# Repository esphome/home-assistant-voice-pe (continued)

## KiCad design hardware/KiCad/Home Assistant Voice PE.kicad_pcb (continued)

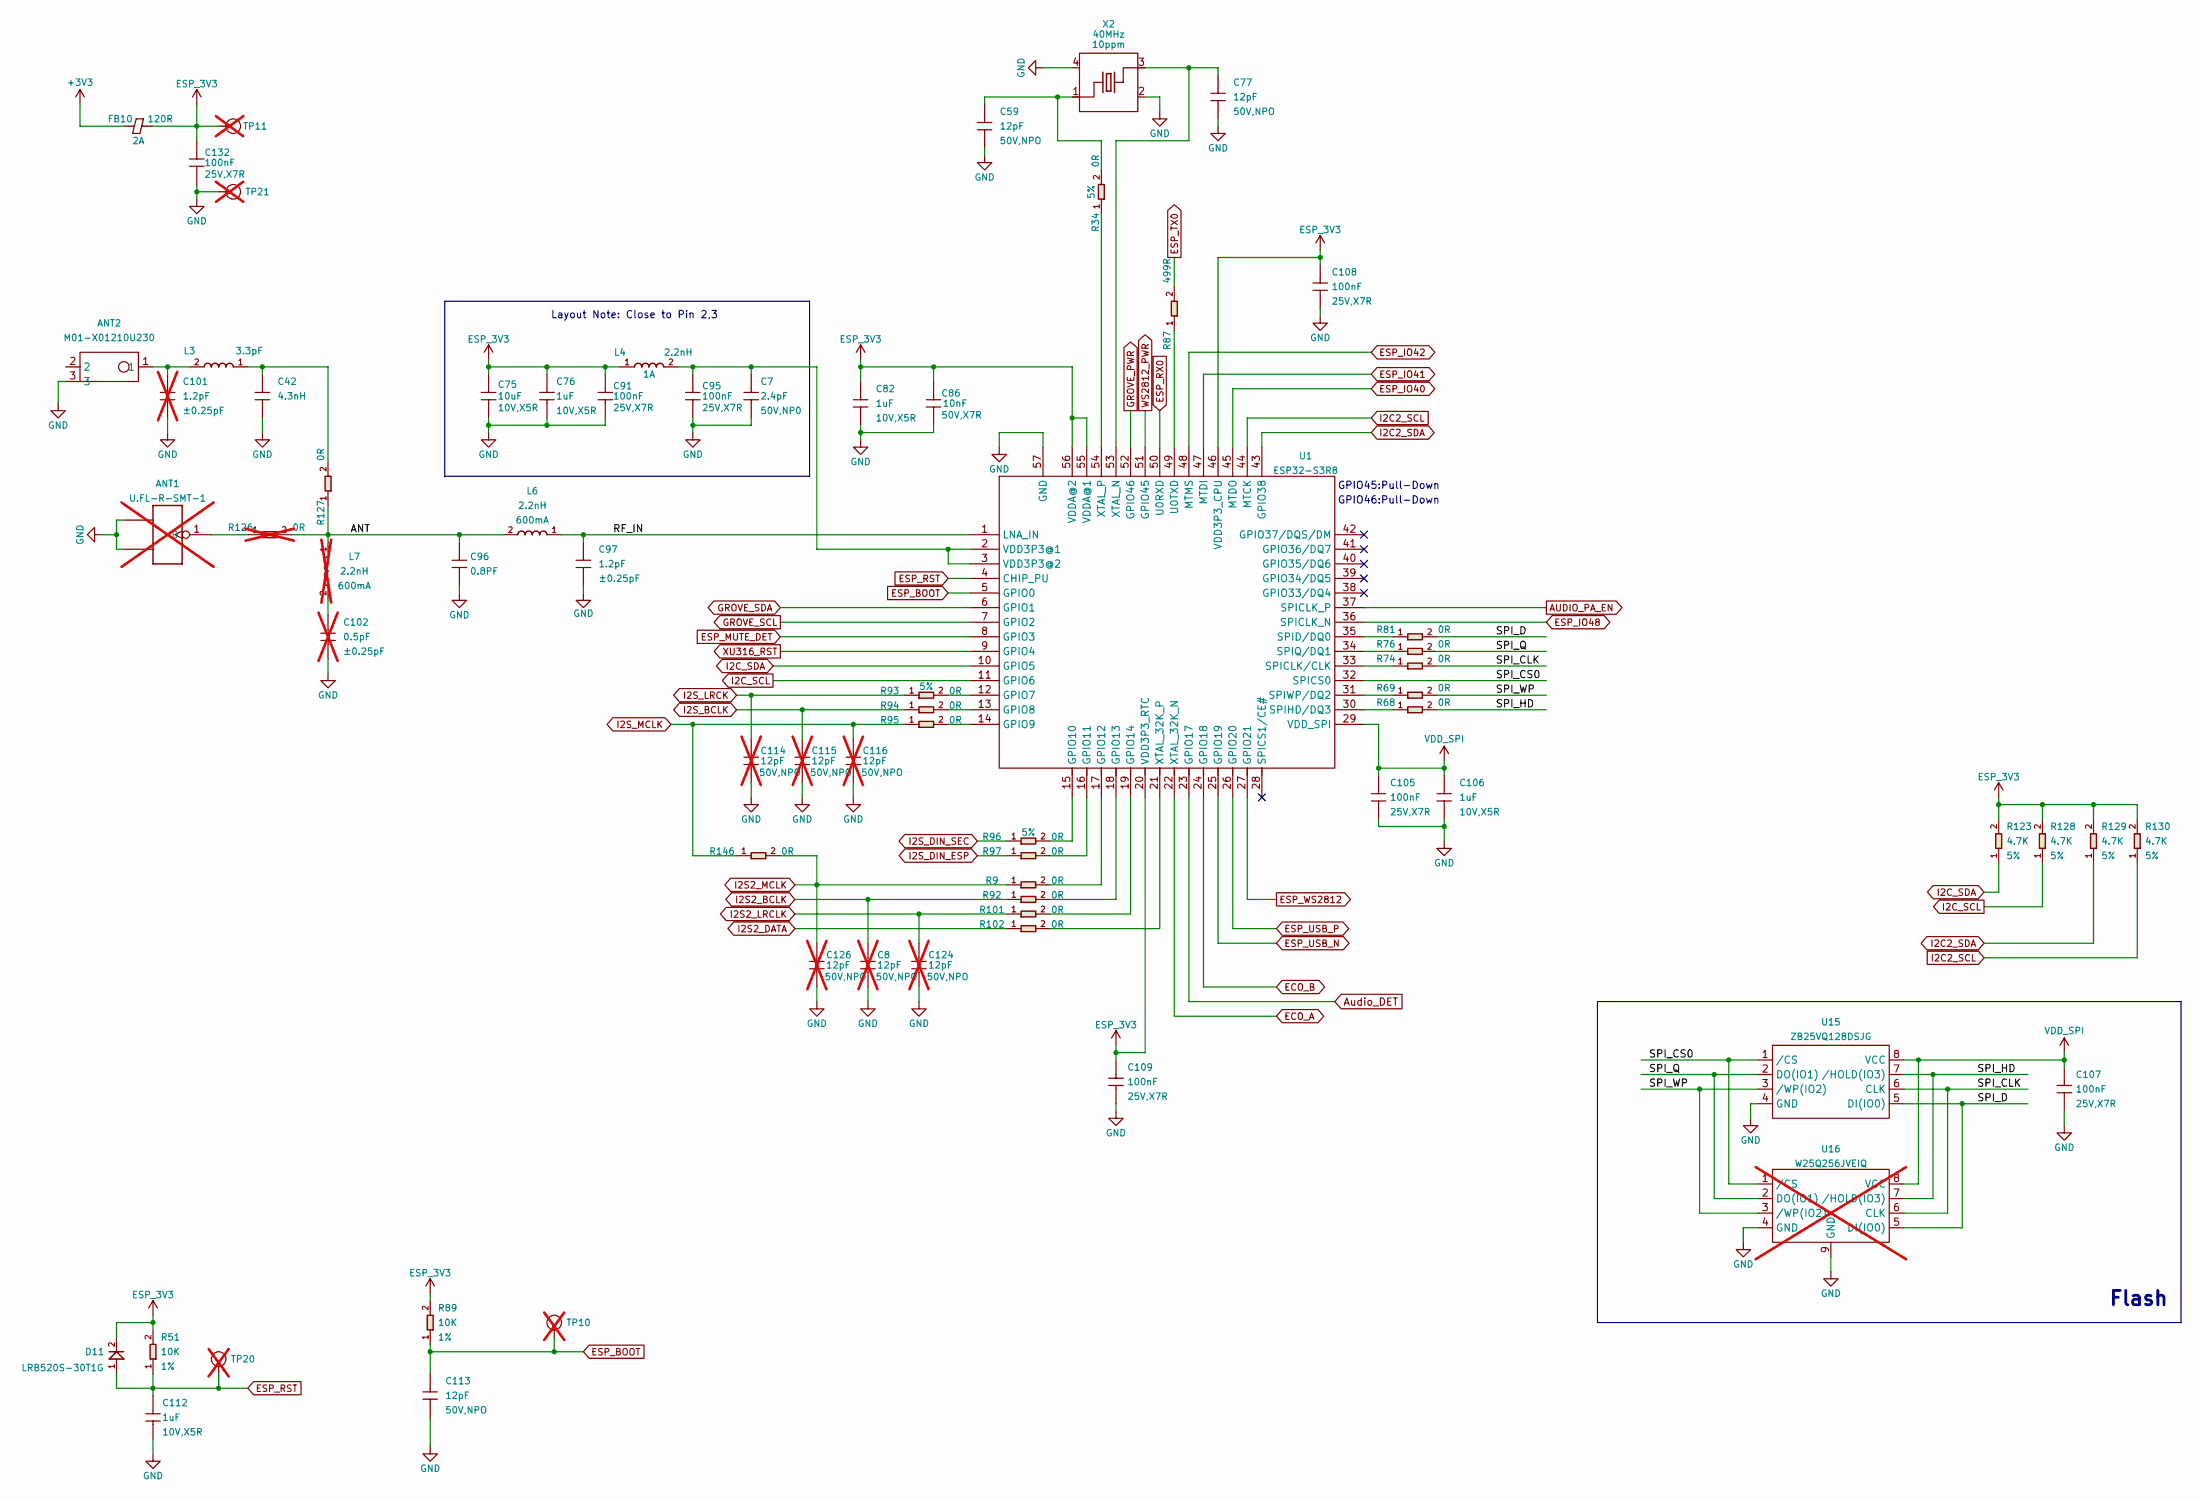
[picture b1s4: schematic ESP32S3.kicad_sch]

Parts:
ANT1: U.FL-R-SMT-1; U-FL3P-SMD-2.6X2.6X1.0MM; MPN U.FL-R-SMT-1; not fitted
ANT2: M01-X01210U230; ANT2P-12x10.45x3.0MM_3; MPN M01-X01210U230
C7: 2.4pF; C0402; Voltage Rating 50V,NP0; MPN CC0402CRNPO9BN2R4
C8, C114, C115, C116, C124, C126: 12pF; C0402; Voltage Rating 50V,NPO; MPN CC0402JRNPO9BN120; not fitted
C42: 4.3nH; C0201; MPN LQP03TN4N3H02D
C59, C77, C113: 12pF; C0402; Voltage Rating 50V,NPO; MPN CC0402JRNPO9BN120
C75: 10uF; C0603; Voltage Rating 10V,X5R; MPN CL10A106KP8NNNC
C76, C82, C106, C112: 1uF; C0402; Voltage Rating 10V,X5R; MPN CL05A105KP5NNNC
C86: 10nF; C0402; Voltage Rating 50V,X7R; MPN CC0402KRX7R9BB103
C91, C95, C105, C107, C108, C109, C132: 100nF; C0402; Voltage Rating 25V,X7R; MPN CC0402KRX7R8BB104
C96: 0.8PF; C0201; Voltage Rating 50V-0.01pF-C0G/NP0; MPN GRM0335C1HR80BA01D
C97: 1.2pF; C0201; Voltage Rating ±0.25pF; MPN CC0201CRNPO9BN1R2
C101: 1.2pF; C0201; Voltage Rating ±0.25pF; MPN CC0201CRNPO9BN1R2; not fitted
C102: 0.5pF; C0201; Voltage Rating ±0.25pF; MPN CC0201CRNPO9BN1R2; not fitted
D11: LRB520S-30T1G; SOD-523; Rating 30V,200mA; MPN LRB520S-30T1G
FB10: 120R; L0603; Rating 2A; MPN BLM18PG121SN1D
L3: 3.3pF; L0201; MPN CQ0201BRNPO8BN3R3
L4: 2.2nH; L0402; Rating 1A; MPN LQW15AN2N2C10D
L6: 2.2nH; L0201; Rating 600mA; MPN LQP03TQ2N2B02D
L7: 2.2nH; L0201; Rating 600mA; MPN LQP03TN1N5B02D; not fitted
R9, R34, R92, R93, R94, R95, R96, R97, R101, R102, R146: 0R; R0402; Power Rating 5%; MPN RC0402JR-070RL
R51, R89: 10K; R0402; Power Rating 1%; MPN RC0402FR-0710KL
R68, R69, R74, R76, R81, R127: 0R; R0201; Power Rating 1%; MPN RC0201FR-070RL
R87: 499R; R0402; Power Rating 1%; MPN RC0402FR-07499RL
R123, R128, R129, R130: 4.7K; R0402; Power Rating 5%; MPN RC0402JR-074K7L
R126: 0R; R0201; Power Rating 1%; MPN RC0201FR-070RL; not fitted
TP10, TP20, TP21: Test Point; TP-D45MIL; Part Type Test Point; not fitted
TP11: TEST-POINT; TP-D45MIL; not fitted
U1: ESP32-S3R8; QFN56G-0.4-7X7MM; MPN ESP32-S3R8
U15: ZB25VQ128DSJG; SOIC8-1.27-5.3X5.3MM; MPN ZB25VQ128DSJG
U16: W25Q256JVEIQ; WSON8-1.27-8x6x0.75mm; MPN W25Q256JVEIQ; not fitted
X2: 40MHz; X4-SMD-2.0X1.6MM; Rating 10ppm; MPN Y4000Fc001

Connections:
+3V3: FB10.1; also elsewhere on the board
/ESP32/ANT: C96.1, L6.2, L7.1, R126.2, R127.1
/ESP32/RF_IN: C97.1, L6.1, U1.1 (LNA_IN)
/ESP32/SPI_CLK: R74.2, U15.6 (CLK), U16.6 (CLK)
/ESP32/SPI_CS0: U1.32 (SPICS0), U15.1 (/CS), U16.1 (/CS)
/ESP32/SPI_D: R81.2, U15.5 (DI(IO0)), U16.5 (DI(IO0))
/ESP32/SPI_HD: R68.2, U15.7 (/HOLD(IO3)), U16.7 (/HOLD(IO3))
/ESP32/SPI_Q: R76.2, U15.2 (DO(IO1)), U16.2 (DO(IO1))
/ESP32/SPI_WP: R69.2, U15.3 (/WP(IO2)), U16.3 (/WP(IO2))
AUDIO_PA_EN: U1.37 (SPICLK_P); also elsewhere on the board
Audio_DET: U1.23 (GPIO17); also elsewhere on the board
ECO_A: U1.22 (XTAL_32K_N); also elsewhere on the board
ECO_B: U1.24 (GPIO18); also elsewhere on the board
ESP_3V3: C75.1, C76.1, C82.1, C86.1, C91.1, C108.1, C109.1, C132.1, D11.2, FB10.2, L4.1, R51.2, R89.2, R123.2, R128.2, R129.2, R130.2, TP11.1 (T), U1.20 (VDD3P3_RTC), U1.46 (VDD3P3_CPU), U1.55 (VDDA@1), U1.56 (VDDA@2); also elsewhere on the board
ESP_BOOT: C113.1, R89.1, TP10.1 (T), U1.5 (GPIO0); also elsewhere on the board
ESP_IO40: U1.45 (MTDO); also elsewhere on the board
ESP_IO41: U1.47 (MTDI); also elsewhere on the board
ESP_IO42: U1.48 (MTMS); also elsewhere on the board
ESP_IO48: U1.36 (SPICLK_N); also elsewhere on the board
ESP_MUTE_DET: U1.8 (GPIO3); also elsewhere on the board
ESP_RST: C112.1, D11.1, R51.1, TP20.1 (T), U1.4 (CHIP_PU)
ESP_RX0: U1.50 (U0RXD); also elsewhere on the board
ESP_TX0: R87.2; also elsewhere on the board
ESP_USB_N: U1.25 (GPIO19); also elsewhere on the board
ESP_USB_P: U1.26 (GPIO20); also elsewhere on the board
ESP_WS2812: U1.27 (GPIO21); also elsewhere on the board
GND: ANT1.2 (GND1), ANT1.3 (GND2), ANT2.3, C7.2, C8.2, C42.2, C59.2, C75.2, C76.2, C77.2, C82.2, C86.2, C91.2, C95.2, C96.2, C97.2, C101.2, C102.2, C105.2, C106.2, C107.2, C108.2, C109.2, C112.2, C113.2, C114.2, C115.2, C116.2, C124.2, C126.2, C132.2, TP21.1 (T), U1.57 (GND), U15.4 (GND), U16.4 (GND), U16.9 (GND), X2.2, X2.4; also elsewhere on the board
GROVE_PWR: U1.52 (GPIO46); also elsewhere on the board
GROVE_SCL: U1.7 (GPIO2); also elsewhere on the board
GROVE_SDA: U1.6 (GPIO1); also elsewhere on the board
I2C2_SCL: R130.1, U1.44 (MTCK); also elsewhere on the board
I2C2_SDA: R129.1, U1.43 (GPIO38); also elsewhere on the board
I2C_SCL: R128.1, U1.11 (GPIO6); also elsewhere on the board
I2C_SDA: R123.1, U1.10 (GPIO5); also elsewhere on the board
I2S2_BCLK: C8.1, R92.1; also elsewhere on the board
I2S2_DATA: R102.1; also elsewhere on the board
I2S2_LRCLK: C124.1, R101.1; also elsewhere on the board
I2S2_MCLK: C126.1, R9.1, R146.2; also elsewhere on the board
I2S_BCLK: C115.1, R94.1; also elsewhere on the board
I2S_DIN_ESP: R97.1; also elsewhere on the board
I2S_DIN_SEC: R96.1; also elsewhere on the board
I2S_LRCK: C114.1, R93.1; also elsewhere on the board
I2S_MCLK: C116.1, R95.1, R146.1; also elsewhere on the board
unnamed: ANT1.1 (D), R126.1
unnamed: ANT2.1, C101.1, L3.2
unnamed: C42.1, L3.1, R127.2
unnamed: C59.1, R34.2, X2.1
unnamed: C102.1, L7.2
unnamed: R93.2, U1.12 (GPIO7)
unnamed: R94.2, U1.13 (GPIO8)
unnamed: R95.2, U1.14 (GPIO9)
unnamed: R96.2, U1.15 (GPIO10)
unnamed: R97.2, U1.16 (GPIO11)
unnamed: R9.2, U1.17 (GPIO12)
unnamed: R92.2, U1.18 (GPIO13)
unnamed: R101.2, U1.19 (GPIO14)
unnamed: R74.1, U1.33 (SPICLK/CLK)
unnamed: R81.1, U1.35 (SPID/DQ0)
unnamed: R68.1, U1.30 (SPIHD/DQ3)
unnamed: R76.1, U1.34 (SPIQ/DQ1)
unnamed: R69.1, U1.31 (SPIWP/DQ2)
unnamed: R87.1, U1.49 (U0TXD)
unnamed: C7.1, C95.1, L4.2, U1.2 (VDD3P3@1), U1.3 (VDD3P3@2)
unnamed: R102.2, U1.21 (XTAL_32K_P)
unnamed: C77.1, U1.53 (XTAL_N), X2.3
unnamed: R34.1, U1.54 (XTAL_P)
VDD_SPI: C105.1, C106.1, C107.1, U1.29 (VDD_SPI), U15.8 (VCC), U16.8 (VCC)
WS2812_PWR: U1.51 (GPIO45); also elsewhere on the board
XU316_RST: U1.9 (GPIO4); also elsewhere on the board

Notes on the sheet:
GPIO45:Pull-Down
Layout Note: Close to Pin 2,3
GPIO46:Pull-Down
Flash

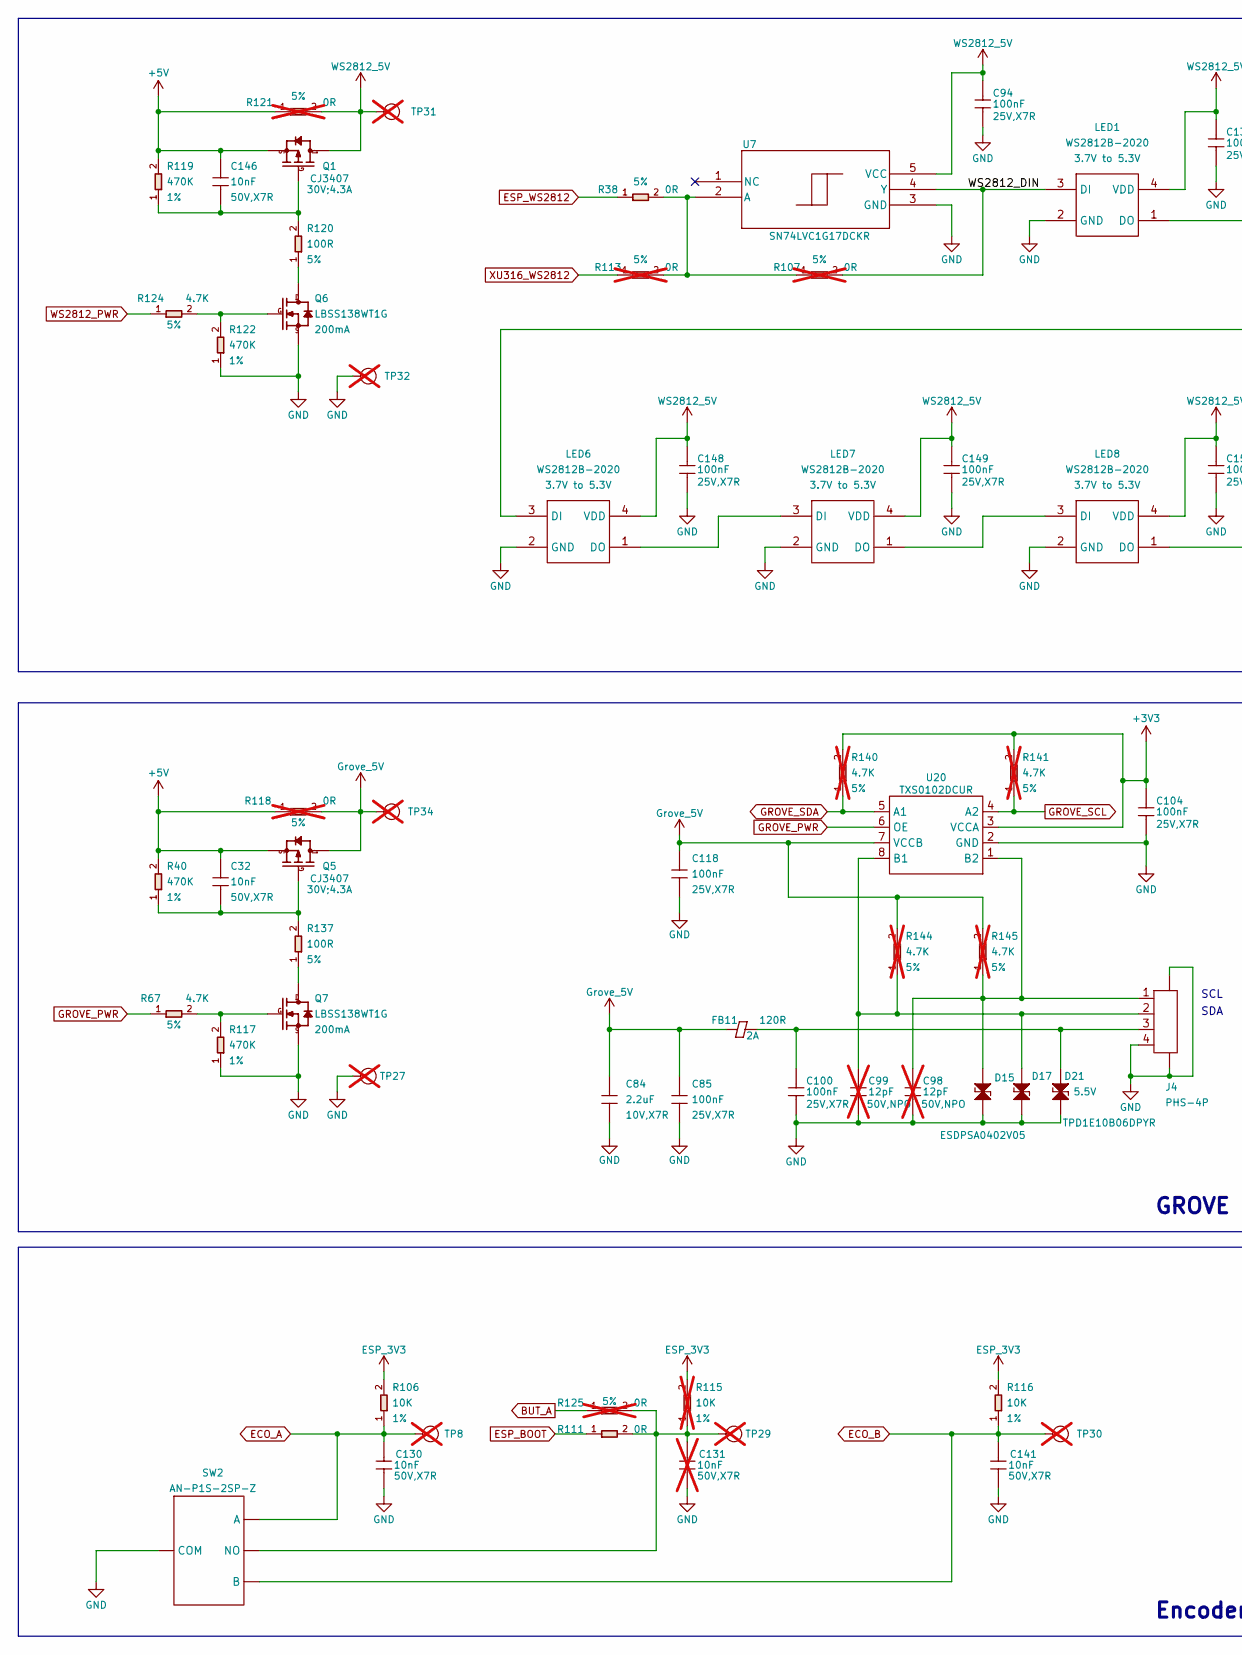
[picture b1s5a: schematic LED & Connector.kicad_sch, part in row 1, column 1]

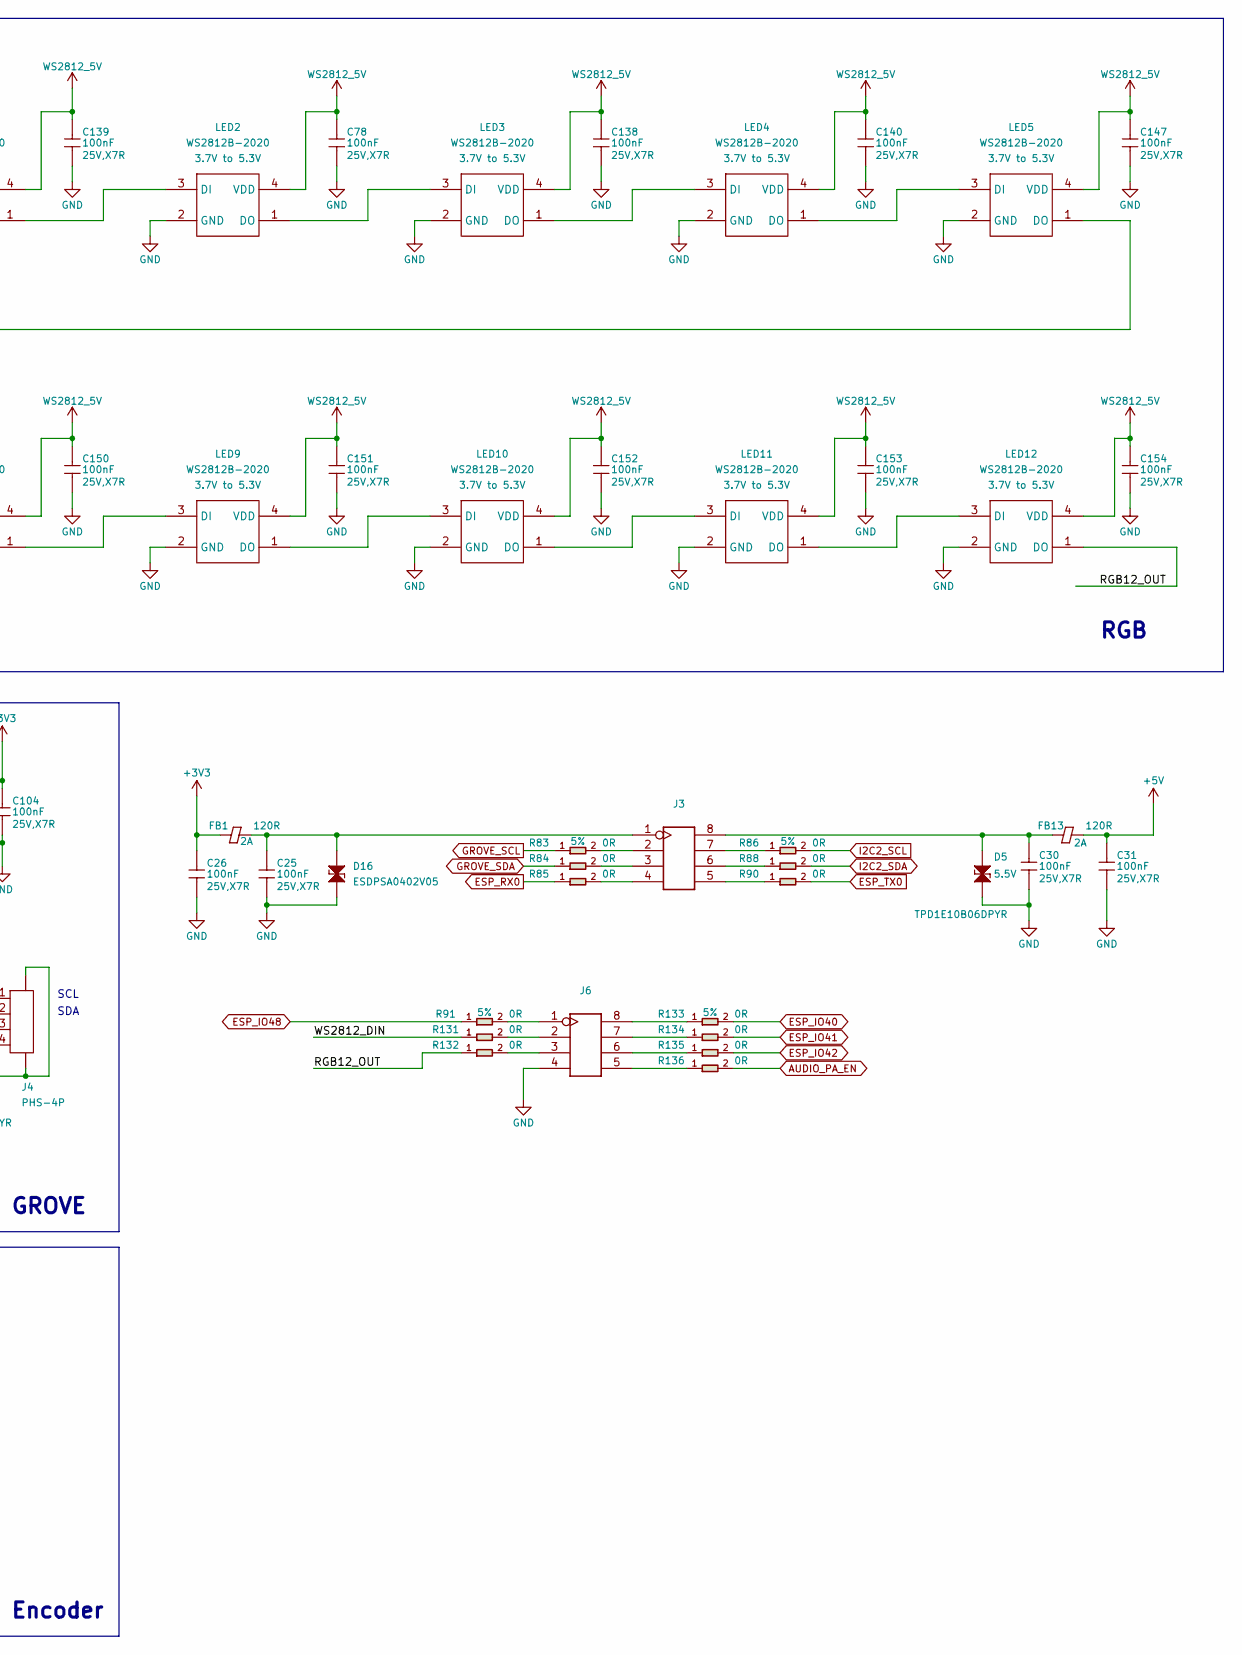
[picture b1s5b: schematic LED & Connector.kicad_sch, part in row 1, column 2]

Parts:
C25, C26, C30, C31, C78, C85, C94, C100, C104, C118, C138, C139, C140, C147, C148, C149, C150, C151, C152, C153, C154: 100nF; C0402; Voltage Rating 25V,X7R; MPN CC0402KRX7R8BB104
C32, C130, C141, C146: 10nF; C0402; Voltage Rating 50V,X7R; MPN CC0402KRX7R9BB103
C84: 2.2uF; C0603; Voltage Rating 10V,X7R; MPN CC0603KRX7R6BB225
C98, C99: 12pF; C0402; Voltage Rating 50V,NPO; MPN CC0402JRNPO9BN120; not fitted
C131: 10nF; C0402; Voltage Rating 50V,X7R; MPN CC0402KRX7R9BB103; not fitted
D5, D21: TPD1E10B06DPYR; ESD-0402; Rating 5.5V; MPN TPD1E10B06DPYR
D15, D16, D17: ESDPSA0402V05; ESD-0402; MPN ESDPSA0402V05
FB1, FB11, FB13: 120R; L0603; Rating 2A; MPN BLM18PG121SN1D
J3, J6: H2X4-2.54-65_35MIL; Part Type Header
J4: PHS-4P; HW4-SMD-2.0; MPN PHS-4P
LED1, LED2, LED3, LED4, LED5, LED6, LED7, LED8, LED9, LED10, LED11, LED12: WS2812B-2020; LED4-1.0-2.2X2X0.84MM; Rating 3.7V to 5.3V; MPN WS2812B-2020
Q1, Q5: CJ3407; SOT23; Rating 30V;4.3A; MPN CJ3407
Q6, Q7: LBSS138WT1G; SOT-323; Rating 200mA; MPN LBSS138WT1G
R38, R83, R84, R85, R86, R88, R90, R91, R111, R131, R132, R133, R134, R135, R136: 0R; R0402; Power Rating 5%; MPN RC0402JR-070RL
R40, R117, R119, R122: 470K; R0402; Power Rating 1%; MPN RC0402FR-07470KL
R67, R124: 4.7K; R0402; Power Rating 5%; MPN RC0402JR-074K7L
R106, R116: 10K; R0402; Power Rating 1%; MPN RC0402FR-0710KL
R107, R113, R125: 0R; R0402; Power Rating 5%; MPN RC0402JR-070RL; not fitted
R115: 10K; R0402; Power Rating 1%; MPN RC0402FR-0710KL; not fitted
R118: 0R; R0603; Power Rating 5%; MPN RC0603JR-070RL; not fitted
R120, R137: 100R; R0402; Power Rating 5%; MPN RC0402JR-07100RL
R121: 0R; R1206; Power Rating 5%; MPN RC1206JR-070RL; not fitted
R140, R141, R144, R145: 4.7K; R0402; Power Rating 5%; MPN RC0402JR-074K7L; not fitted
SW2: AN-P1S-2SP-Z; MPN AN-P1S-2SP-Z
TP8: TEST-POINT; TP-D45MIL; not fitted
TP27, TP29, TP30, TP31, TP32, TP34: Test Point; TP-D45MIL; Part Type Test Point; not fitted
U7: SN74LVC1G17DCKR; MPN SN74LVC1G17DCKR
U20: TXS0102DCUR; VSSOP8-0.5-2.3X2X0.9MM; MPN TXS0102DCUR

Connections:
+3V3: C26.1, C104.1, FB1.1, R140.2, R141.2, U20.3 (VCCA); also elsewhere on the board
+5V: C31.1, C32.1, C146.1, FB13.2, Q1.2 (S), Q5.2 (S), R40.2, R118.1, R119.2, R121.1; also elsewhere on the board
/LED & Connector/RGB12_OUT: LED12.1 (DO), R132.1
/LED & Connector/WS2812_DIN: LED1.3 (DI), R107.2, R131.1, U7.4 (Y)
AUDIO_PA_EN: R136.2; also elsewhere on the board
BUT_A: R125.1; also elsewhere on the board
ECO_A: C130.1, R106.1, SW2.A, TP8.1 (T); also elsewhere on the board
ECO_B: C141.1, R116.1, SW2.B, TP30.1 (T); also elsewhere on the board
ESP_3V3: R106.2, R115.2, R116.2; also elsewhere on the board
ESP_BOOT: R111.1; also elsewhere on the board
ESP_IO40: R133.2; also elsewhere on the board
ESP_IO41: R134.2; also elsewhere on the board
ESP_IO42: R135.2; also elsewhere on the board
ESP_IO48: R91.1; also elsewhere on the board
ESP_RX0: R85.1; also elsewhere on the board
ESP_TX0: R90.2; also elsewhere on the board
ESP_WS2812: R38.1; also elsewhere on the board
GND: C25.2, C26.2, C30.2, C31.2, C78.2, C84.2, C85.2, C94.2, C98.2, C99.2, C100.2, C104.2, C118.2, C130.2, C131.2, C138.2, C139.2, C140.2, C141.2, C147.2, C148.2, C149.2, C150.2, C151.2, C152.2, C153.2, C154.2, D5.1, D15.1, D16.1, D17.1, D21.1, J4.4, J4.5, J4.6, J6.4, LED1.2 (GND), LED2.2 (GND), LED3.2 (GND), LED4.2 (GND), LED5.2 (GND), LED6.2 (GND), LED7.2 (GND), LED8.2 (GND), LED9.2 (GND), LED10.2 (GND), LED11.2 (GND), LED12.2 (GND), Q6.2 (S), Q7.2 (S), R117.1, R122.1, SW2.COM, TP27.1 (T), TP32.1 (T), U7.3 (GND), U20.2 (GND); also elsewhere on the board
GROVE_PWR: R67.1, U20.6 (OE); also elsewhere on the board
GROVE_SCL: R83.1, R141.1, U20.4 (A2); also elsewhere on the board
GROVE_SDA: R84.1, R140.1, U20.5 (A1); also elsewhere on the board
Grove_5V: C84.1, C85.1, C118.1, FB11.1, Q5.3 (D), R118.2, R144.2, R145.2, TP34.1 (T), U20.7 (VCCB)
I2C2_SCL: R86.2; also elsewhere on the board
I2C2_SDA: R88.2; also elsewhere on the board
unnamed: C25.1, D16.2, FB1.2, J3.1
unnamed: C30.1, D5.2, FB13.1, J3.8
unnamed: C100.1, D21.2, FB11.2, J4.3
unnamed: J3.2, R83.2
unnamed: J3.3, R84.2
unnamed: J3.4, R85.2
unnamed: J3.5, R90.1
unnamed: J3.6, R88.1
unnamed: J3.7, R86.1
unnamed: J6.1, R91.2
unnamed: J6.2, R131.2
unnamed: J6.3, R132.2
unnamed: J6.5, R136.1
unnamed: J6.6, R135.1
unnamed: J6.7, R134.1
unnamed: J6.8, R133.1
unnamed: LED1.1 (DO), LED2.3 (DI)
unnamed: LED2.1 (DO), LED3.3 (DI)
unnamed: LED3.1 (DO), LED4.3 (DI)
unnamed: LED4.1 (DO), LED5.3 (DI)
unnamed: LED5.1 (DO), LED6.3 (DI)
unnamed: LED6.1 (DO), LED7.3 (DI)
unnamed: LED7.1 (DO), LED8.3 (DI)
unnamed: LED8.1 (DO), LED9.3 (DI)
unnamed: LED9.1 (DO), LED10.3 (DI)
unnamed: LED10.1 (DO), LED11.3 (DI)
unnamed: LED11.1 (DO), LED12.3 (DI)
unnamed: C146.2, Q1.1 (G), R119.1, R120.2
unnamed: C32.2, Q5.1 (G), R40.1, R137.2
unnamed: Q6.3 (D), R120.1
unnamed: Q6.1 (G), R122.2, R124.2
unnamed: Q7.3 (D), R137.1
unnamed: Q7.1 (G), R67.2, R117.2
unnamed: C131.1, R111.2, R115.1, R125.2, SW2.NO, TP29.1 (T)
unnamed: R38.2, R107.1, R113.2, U7.2 (A)
unnamed: C99.1, D17.2, J4.2, R144.1, U20.8 (B1)
unnamed: C98.1, D15.2, J4.1, R145.1, U20.1 (B2)
WS2812_5V: C78.1, C94.1, C138.1, C139.1, C140.1, C147.1, C148.1, C149.1, C150.1, C151.1, C152.1, C153.1, C154.1, LED1.4 (VDD), LED2.4 (VDD), LED3.4 (VDD), LED4.4 (VDD), LED5.4 (VDD), LED6.4 (VDD), LED7.4 (VDD), LED8.4 (VDD), LED9.4 (VDD), LED10.4 (VDD), LED11.4 (VDD), LED12.4 (VDD), Q1.3 (D), R121.2, TP31.1 (T), U7.5 (VCC)
WS2812_PWR: R124.1; also elsewhere on the board
XU316_WS2812: R113.1; also elsewhere on the board

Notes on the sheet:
Encoder
SCL
SDA
GROVE
RGB

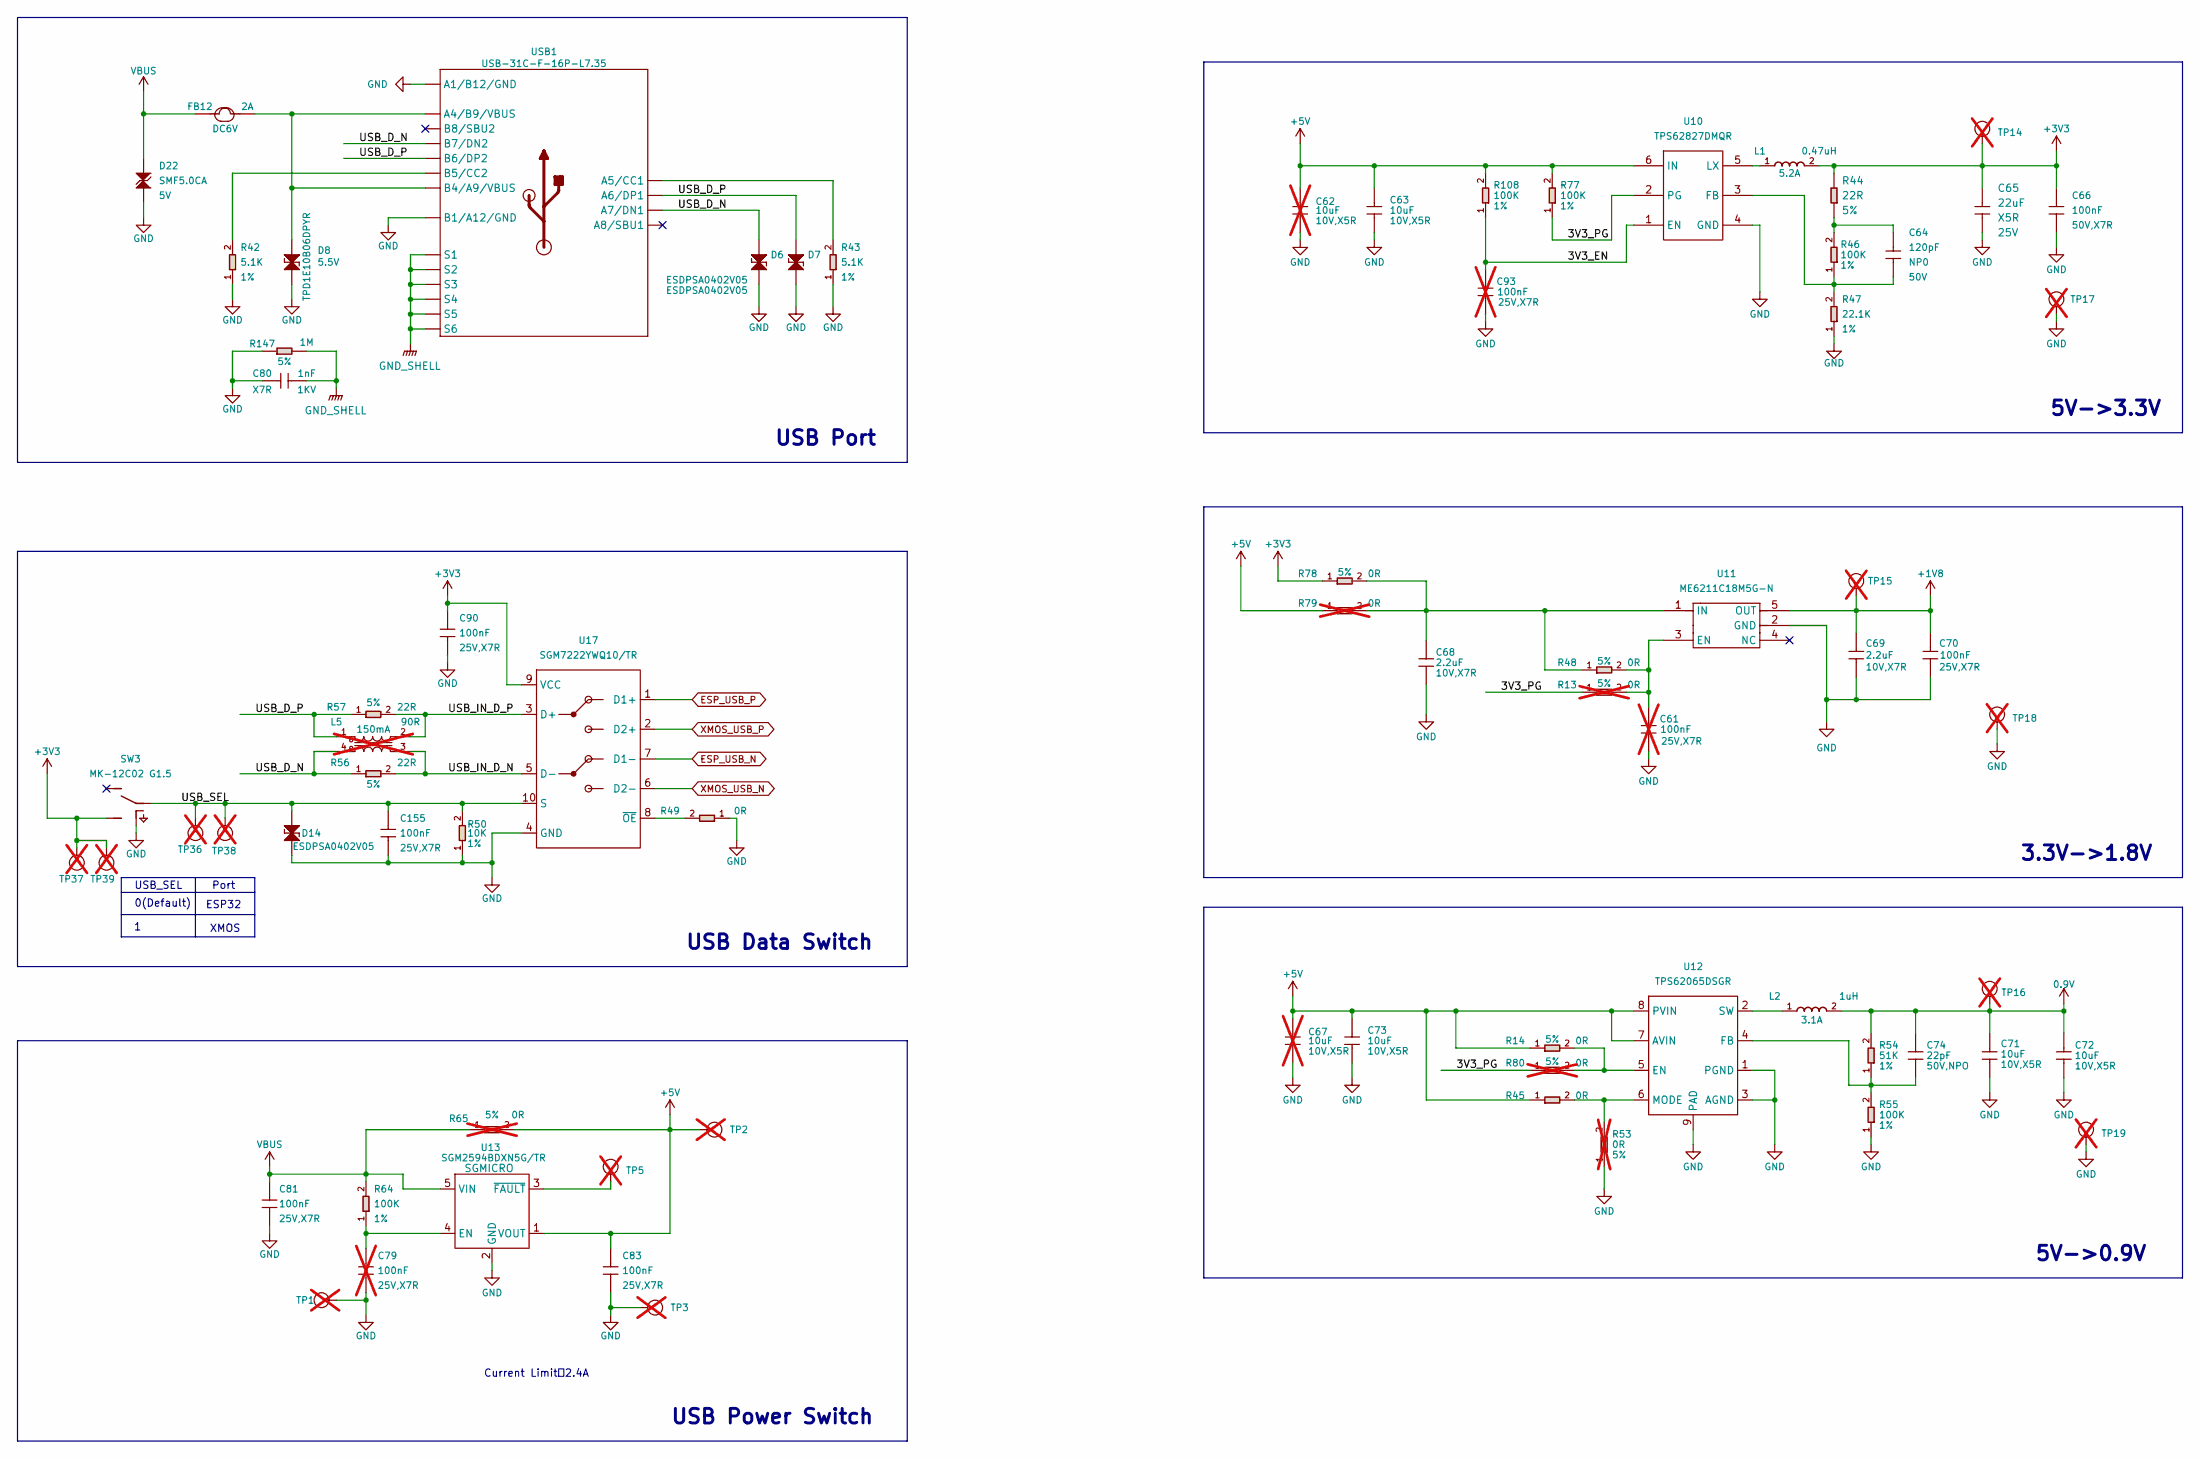
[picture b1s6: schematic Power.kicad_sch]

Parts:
C61, C79, C93: 100nF; C0402; Voltage Rating 25V,X7R; MPN CC0402KRX7R8BB104; not fitted
C62, C67: 10uF; C0603; Voltage Rating 10V,X5R; MPN CL10A106KP8NNNC; not fitted
C63, C71, C72, C73: 10uF; C0603; Voltage Rating 10V,X5R; MPN CL10A106KP8NNNC
C64: 120pF; C0402; Voltage Rating 50V; MPN CC0402JRNPO9BN121
C65: 22uF; C0805; Voltage Rating 25V; MPN CL21A226MAYNNNE
C66: 100nF; C0603; Voltage Rating 50V,X7R; MPN CC0603KRX7R9BB104
C68, C69: 2.2uF; C0603; Voltage Rating 10V,X7R; MPN CC0603KRX7R6BB225
C70, C81, C83, C90, C155: 100nF; C0402; Voltage Rating 25V,X7R; MPN CC0402KRX7R8BB104
C74: 22pF; C0402; Voltage Rating 50V,NPO; MPN CC0402JRNPO9BN220
C80: 1nF; C1206; Voltage Rating 1KV; MPN CC1206KKX7RCBB102
D6, D7, D14: ESDPSA0402V05; ESD-0402; MPN ESDPSA0402V05
D8: TPD1E10B06DPYR; ESD-0402; Rating 5.5V; MPN TPD1E10B06DPYR
D22: SMF5.0CA; SOD-123; Rating 5V; MPN SMF5.0CA
FB12: 2A; F1206; Rating DC6V; MPN SMD1206R200SF
L1: 0.47uH; L0805; Rating 5.2A; MPN WPN201610MR47MT
L2: 1uH; L2016; Rating 3.1A; MPN WPN201610U1R0MTY01
L5: 90R; INT4-SMD-1X1.25X0.82MM; Rating 150mA; MPN DLP11SN900HL2L; not fitted
R13, R53, R79, R80: 0R; R0402; Power Rating 5%; MPN RC0402JR-070RL; not fitted
R14, R45, R48, R49, R78: 0R; R0402; Power Rating 5%; MPN RC0402JR-070RL
R42, R43: 5.1K; R0402; Power Rating 1%; MPN RC0402FR-075K1L
R44, R56, R57: 22R; R0402; Power Rating 5%; MPN RC0402JR-0722RL
R46, R55, R64, R77, R108: 100K; R0402; Power Rating 1%; MPN RC0402FR-07100KL
R47: 22.1K; R0402; Power Rating 1%; MPN RC0402FR-0722K1L
R50: 10K; R0402; Power Rating 1%; MPN RC0402FR-0710KL
R54: 51K; R0402; Power Rating 1%; MPN RC0402FR-0751KL
R65: 0R; R1206; Power Rating 5%; MPN RC1206JR-070RL; not fitted
R147: 1M; R0805; Power Rating 5%; MPN RC0805JR-071ML
SW3: MK-12C02 G1.5; SW7-SMD-L6.7X2.7X3.2MM; MPN MK-12C02 G1.5
TP1, TP5, TP14, TP15, TP16, TP17, TP18, TP19: TEST-POINT; TP-D45MIL; not fitted
TP2, TP3: Test Point; TP-1.6MM-ROUND; Part Type Test Point; not fitted
TP36, TP37: Test Point; TP-D120MIL; Part Type Test Point; not fitted
TP38, TP39: Test Point; TP-D45MIL; Part Type Test Point; not fitted
U10: TPS62827DMQR; DFN6-0.5-1.5X1.5X0.65MM; MPN TPS62827DMQR
U11: ME6211C18M5G-N; SOT-23-5; MPN ME6211C18M5G-N
U12: TPS62065DSGR; DFN8G-0.5-2X2MM; MPN TPS62065DSGR
U13: SGM2594BDXN5G/TR; SOT-23-5; MPN SGM2594BDXN5G/TR
U17: SGM7222YWQ10/TR; WQFN10_0d4_1_8x1_4x0_75mm; MPN SGM7222YWQ10/TR
USB1: USB-31C-F-16P-L7.35; USB2.0-TYPE-C; MPN USB-31C-F-16P-L7.35

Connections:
0.9V: C71.1, C72.1, C74.1, L2.2, R54.2, TP16.1 (T); also elsewhere on the board
+1V8: C69.1, C70.1, TP15.1 (T), U11.5 (OUT); also elsewhere on the board
+3V3: C65.1, C66.1, C90.1, L1.2, R44.2, R78.1, SW3.3 (B), TP14.1 (T), TP37.1 (T), TP39.1 (T), U17.9 (VCC); also elsewhere on the board
+5V: C62.1, C63.1, C67.1, C73.1, C83.1, R14.1, R45.1, R65.2, R77.2, R79.1, R108.2, TP2.1 (T), U10.6 (IN), U12.7 (AVIN), U12.8 (PVIN), U13.1 (VOUT); also elsewhere on the board
/Power/3V3_EN: C93.1, R108.1, U10.1 (EN)
/Power/3V3_PG: R13.1, R77.1, R80.1, U10.2 (PG)
/Power/USB_D_N: D6.2, L5.4, R56.1, USB1.A7 (A7/DN1), USB1.B7 (B7/DN2)
/Power/USB_D_P: D7.2, L5.1, R57.1, USB1.A6 (A6/DP1), USB1.B6 (B6/DP2)
/Power/USB_IN_D_N: L5.3, R56.2, U17.5 (D-)
/Power/USB_IN_D_P: L5.2, R57.2, U17.3 (D+)
/Power/USB_SEL: C155.1, D14.1, R50.2, SW3.2 (COM), TP36.1 (T), TP38.1 (T), U17.10 (S)
ESP_USB_N: U17.7 (D1-); also elsewhere on the board
ESP_USB_P: U17.1 (D1+); also elsewhere on the board
GND: C61.2, C62.2, C63.2, C65.2, C66.2, C67.2, C68.2, C69.2, C70.2, C71.2, C72.2, C73.2, C79.2, C80.1, C81.2, C83.2, C90.2, C93.2, C155.2, D6.1, D7.1, D8.1, D14.2, D22.1, R42.1, R43.1, R47.1, R49.1, R50.1, R53.1, R55.1, R147.1, SW3.P1 (SS2), SW3.P2 (SS2), SW3.P3 (SS2), SW3.P4 (SS2), TP1.1 (T), TP3.1 (T), TP17.1 (T), TP18.1 (T), TP19.1 (T), U10.4 (GND), U11.2 (GND), U12.1 (PGND), U12.3 (AGND), U12.9 (PAD), U13.2 (GND), U17.4 (GND), USB1.A1_B12 (A1/B12/GND), USB1.B1_A12 (B1/A12/GND); also elsewhere on the board
GND_SHELL: C80.2, R147.2, USB1.S1, USB1.S2, USB1.S3, USB1.S4, USB1.S5, USB1.S6
unnamed: C64.1, R44.1, R46.2
unnamed: TP5.1 (T), U13.3 (~FAULT)
unnamed: C64.2, R46.1, R47.2, U10.3 (FB)
unnamed: L1.1, U10.5 (LX)
unnamed: C61.1, R13.2, R48.2, U11.3 (EN)
unnamed: C68.1, R48.1, R78.2, R79.2, U11.1 (IN)
unnamed: R14.2, R80.2, U12.5 (EN)
unnamed: C74.2, R54.1, R55.2, U12.4 (FB)
unnamed: R45.2, R53.2, U12.6 (MODE)
unnamed: L2.1, U12.2 (SW)
unnamed: C79.1, R64.1, U13.4 (EN)
unnamed: R49.2, U17.8 (~OE)
unnamed: D8.2, FB12.2, USB1.A4_B9 (A4/B9/VBUS), USB1.B4_A9 (B4/A9/VBUS)
unnamed: R43.2, USB1.A5 (A5/CC1)
unnamed: R42.2, USB1.B5 (B5/CC2)
VBUS: C81.1, D22.2, FB12.1, R64.2, R65.1, U13.5 (VIN); also elsewhere on the board
XMOS_USB_N: U17.6 (D2-); also elsewhere on the board
XMOS_USB_P: U17.2 (D2+); also elsewhere on the board

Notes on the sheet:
Current Limit：2.4A
USB Port
Port
3.3V->1.8V
0(Default)
5V->0.9V
ESP32
5V->3.3V
USB Power Switch
XMOS
USB Data Switch
USB_SEL
